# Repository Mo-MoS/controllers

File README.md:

# Controllers

## Description

Controllers for MIDI, USB, Software Synths, VST Plugins. 

## Pictures

**PCB boards for the 14 knobs of S2-OSC:**

**Functional prototype of S2-OSC in a livestream:**

**Paper scribble for the S2-OSC frontplate:**

**Prototype in handmade PCB boards for S2-OSC:**

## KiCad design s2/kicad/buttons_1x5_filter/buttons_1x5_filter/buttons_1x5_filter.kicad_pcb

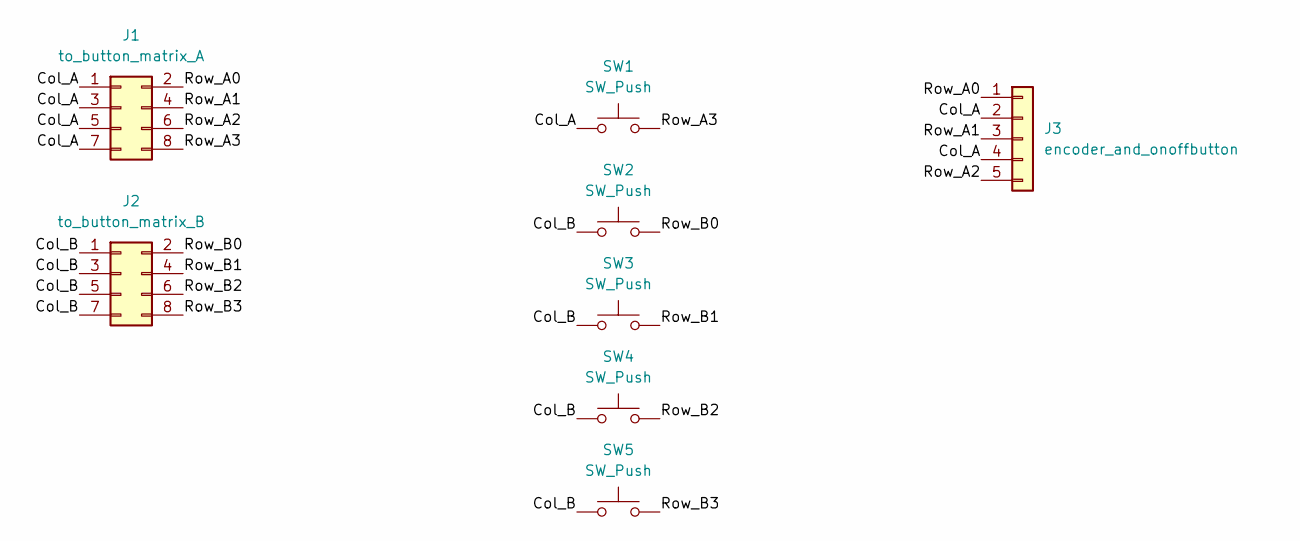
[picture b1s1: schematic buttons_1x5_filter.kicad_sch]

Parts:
J1: to_button_matrix_A; PinHeader_2x04_P2.54mm_Vertical
J2: to_button_matrix_B; PinHeader_2x04_P2.54mm_Vertical
J3: encoder_and_onoffbutton; PinHeader_1x05_P2.54mm_Vertical
SW1, SW2, SW3, SW4, SW5: SW_Push; SW_PUSH_6mm

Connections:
/Col_A: J1.1, J1.3, J1.5, J1.7, J3.2, J3.4, SW1.1
/Col_B: J2.1, J2.3, J2.5, J2.7, SW2.1, SW3.1, SW4.1, SW5.1
/Row_A0: J1.2, J3.1
/Row_A1: J1.4, J3.3
/Row_A2: J1.6, J3.5
/Row_A3: J1.8, SW1.2
/Row_B0: J2.2, SW2.2
/Row_B1: J2.4, SW3.2
/Row_B2: J2.6, SW4.2
/Row_B3: J2.8, SW5.2

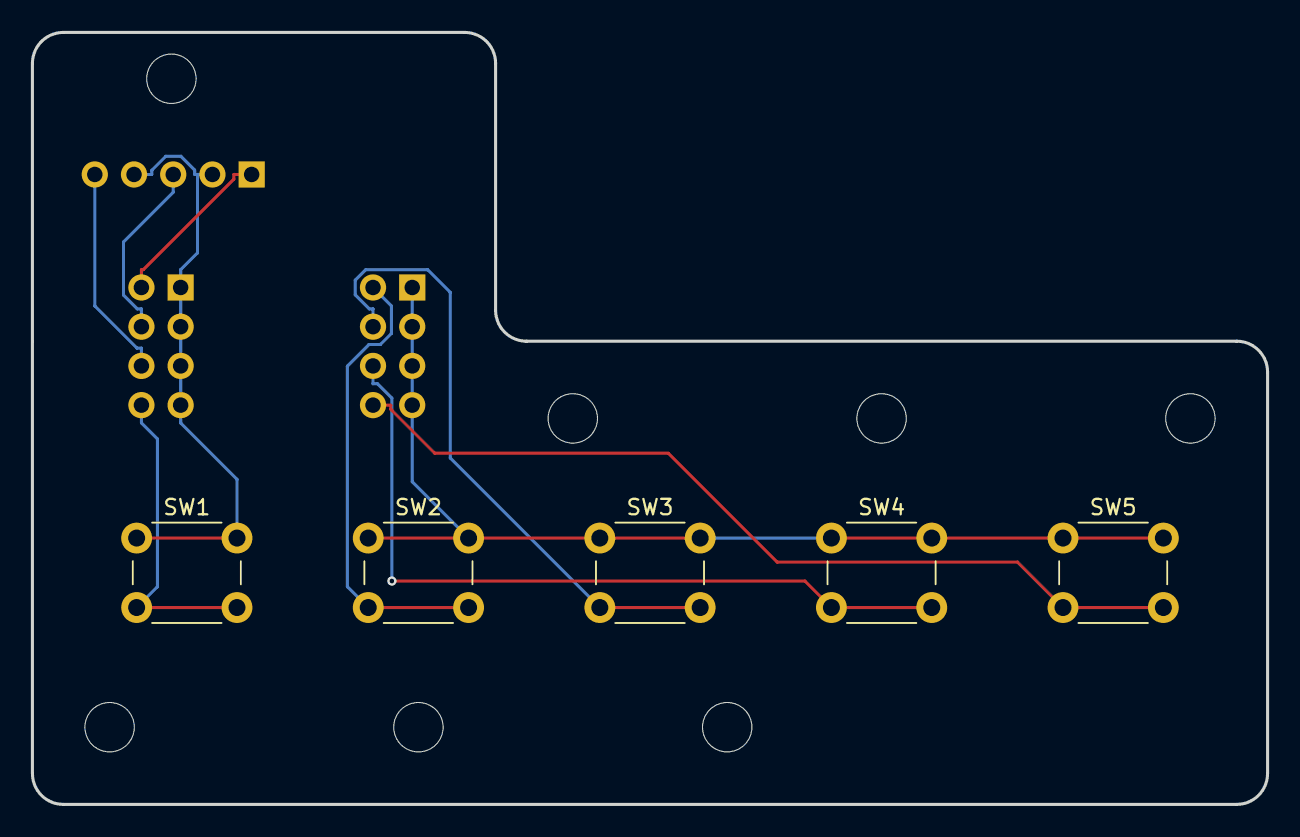
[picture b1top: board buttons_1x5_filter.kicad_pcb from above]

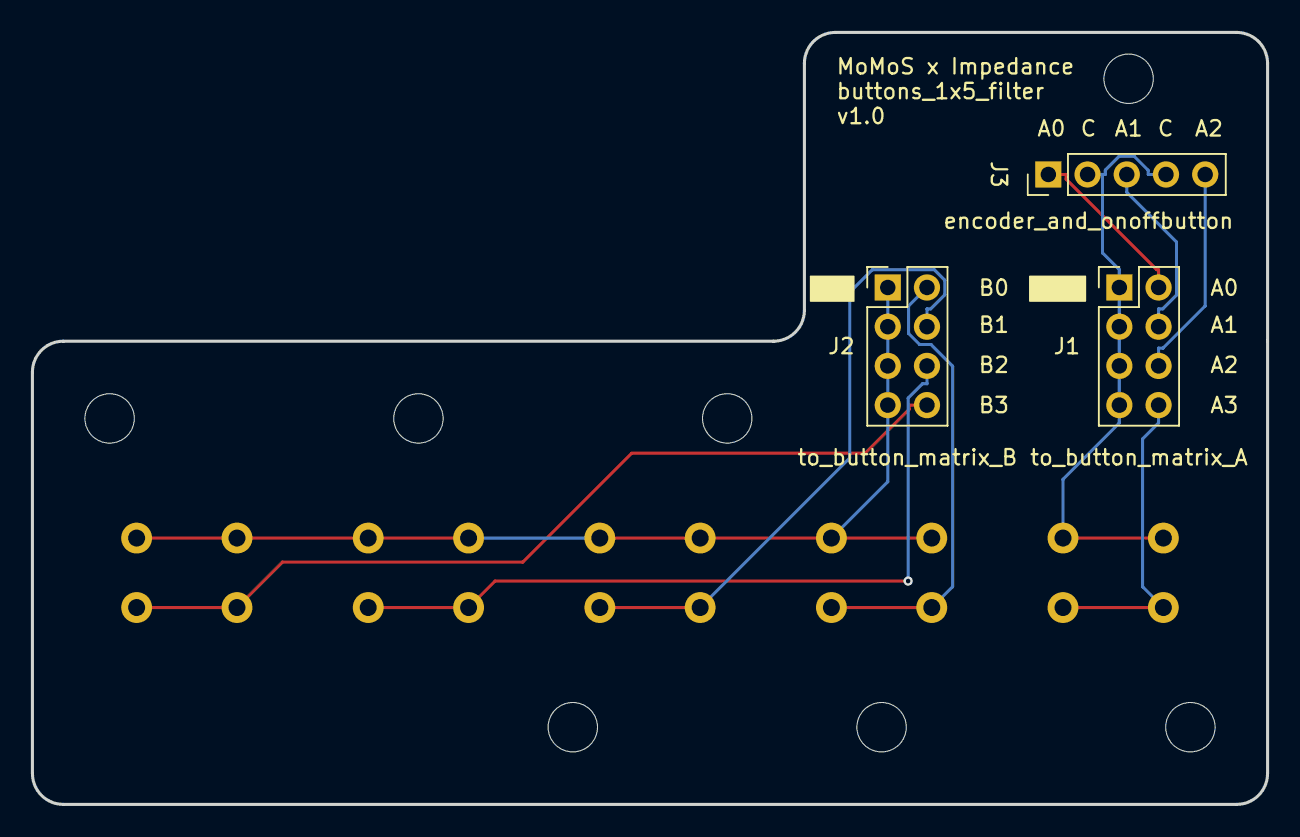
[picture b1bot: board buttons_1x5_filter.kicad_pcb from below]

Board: 2 copper layers, 80.0 x 50.0 mm, 8 parts (3 on the bottom side), 10 nets.

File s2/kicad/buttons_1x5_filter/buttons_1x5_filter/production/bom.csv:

Designator,Footprint,Quantity,Value,LCSC Part #
J1,PinHeader_2x04_P2.54mm_Vertical,1,to_button_matrix_A,
J2,PinHeader_2x04_P2.54mm_Vertical,1,to_button_matrix_B,
J3,PinHeader_1x05_P2.54mm_Vertical,1,encoder_and_onoffbutton,
"SW1, SW2, SW3, SW4, SW5",SW_PUSH_6mm,5,SW_Push,

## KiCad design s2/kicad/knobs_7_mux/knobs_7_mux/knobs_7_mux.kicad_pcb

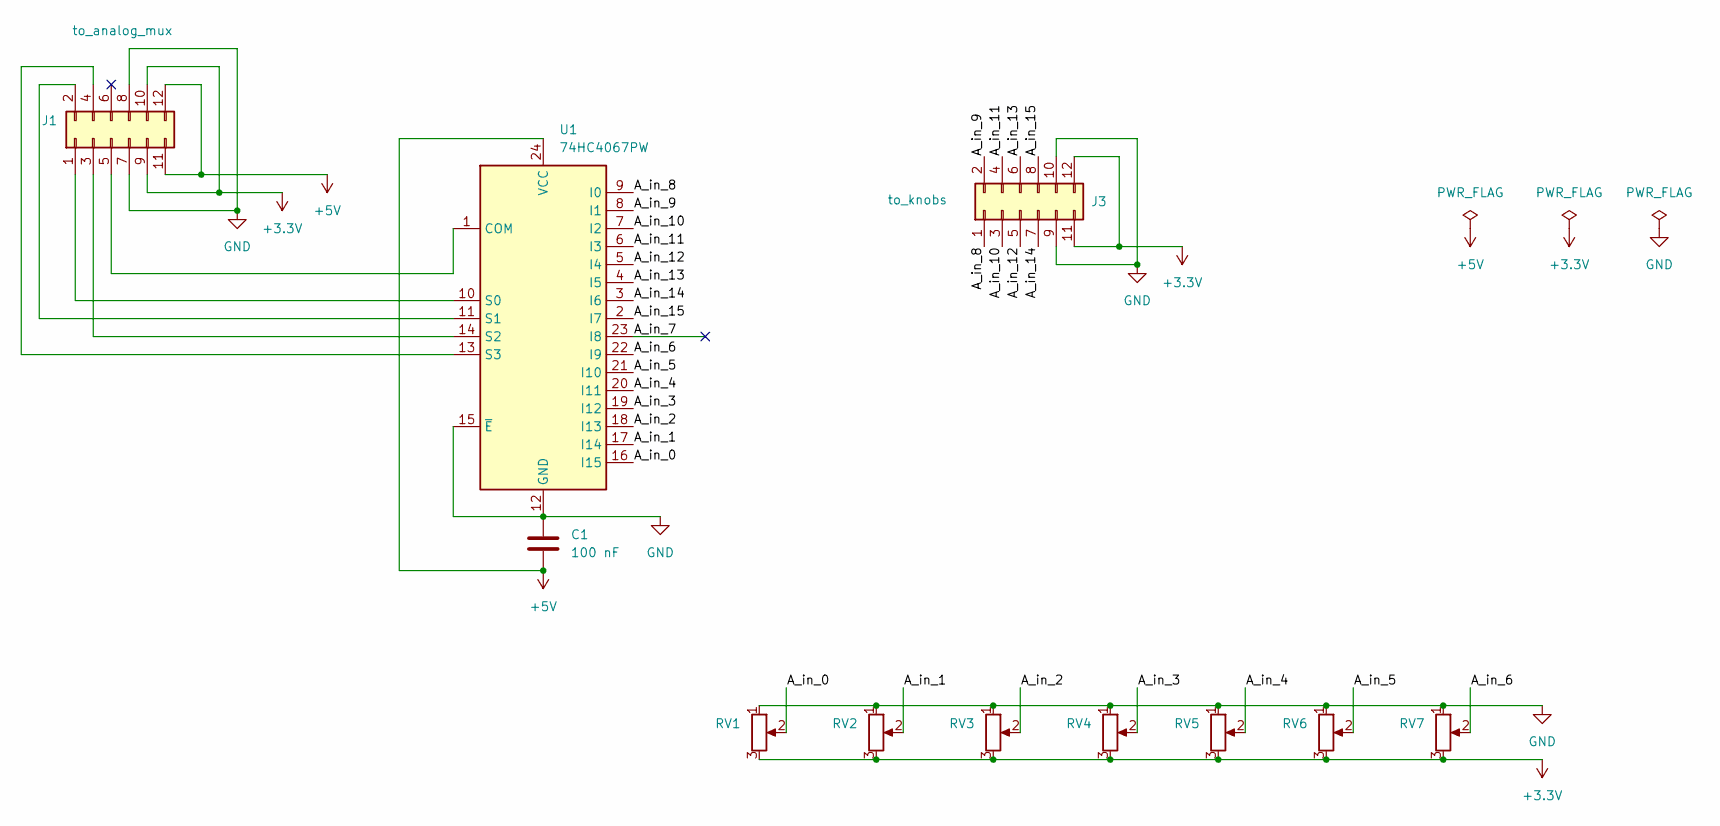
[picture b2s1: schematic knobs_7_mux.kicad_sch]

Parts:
C1: 100 nF; C_0402_1005Metric
J1: to_analog_mux; PinHeader_2x06_P2.54mm_Vertical
J3: to_knobs; PinHeader_2x06_P2.54mm_Vertical
RV1, RV2, RV3, RV4, RV5, RV6, RV7: R_Potentiometer; Potentiometer_RV09
U1: 74HC4067PW; SOP-24_7.5x15.4mm_P1.27mm

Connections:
+3.3V: J1.9, J1.10, J3.11, J3.12, RV1.3, RV2.3, RV3.3, RV4.3, RV5.3, RV6.3, RV7.3
+5V: C1.2, J1.11, J1.12, U1.24 (VCC)
/A_in_0: RV1.2, U1.16 (I15)
/A_in_1: RV2.2, U1.17 (I14)
/A_in_2: RV3.2, U1.18 (I13)
/A_in_3: RV4.2, U1.19 (I12)
/A_in_4: RV5.2, U1.20 (I11)
/A_in_5: RV6.2, U1.21 (I10)
/A_in_6: RV7.2, U1.22 (I9)
/A_in_7: U1.23 (I8)
/A_in_8: J3.1, U1.9 (I0)
/A_in_9: J3.2, U1.8 (I1)
/A_in_10: J3.3, U1.7 (I2)
/A_in_11: J3.4, U1.6 (I3)
/A_in_12: J3.5, U1.5 (I4)
/A_in_13: J3.6, U1.4 (I5)
/A_in_14: J3.7, U1.3 (I6)
/A_in_15: J3.8, U1.2 (I7)
GND: C1.1, J1.7, J1.8, J3.9, J3.10, RV1.1, RV2.1, RV3.1, RV4.1, RV5.1, RV6.1, RV7.1, U1.12 (GND), U1.15 (~E)
unnamed: J1.1, U1.10 (S0)
unnamed: J1.2, U1.11 (S1)
unnamed: J1.3, U1.14 (S2)
unnamed: J1.4, U1.13 (S3)
unnamed: J1.5, U1.1 (COM)

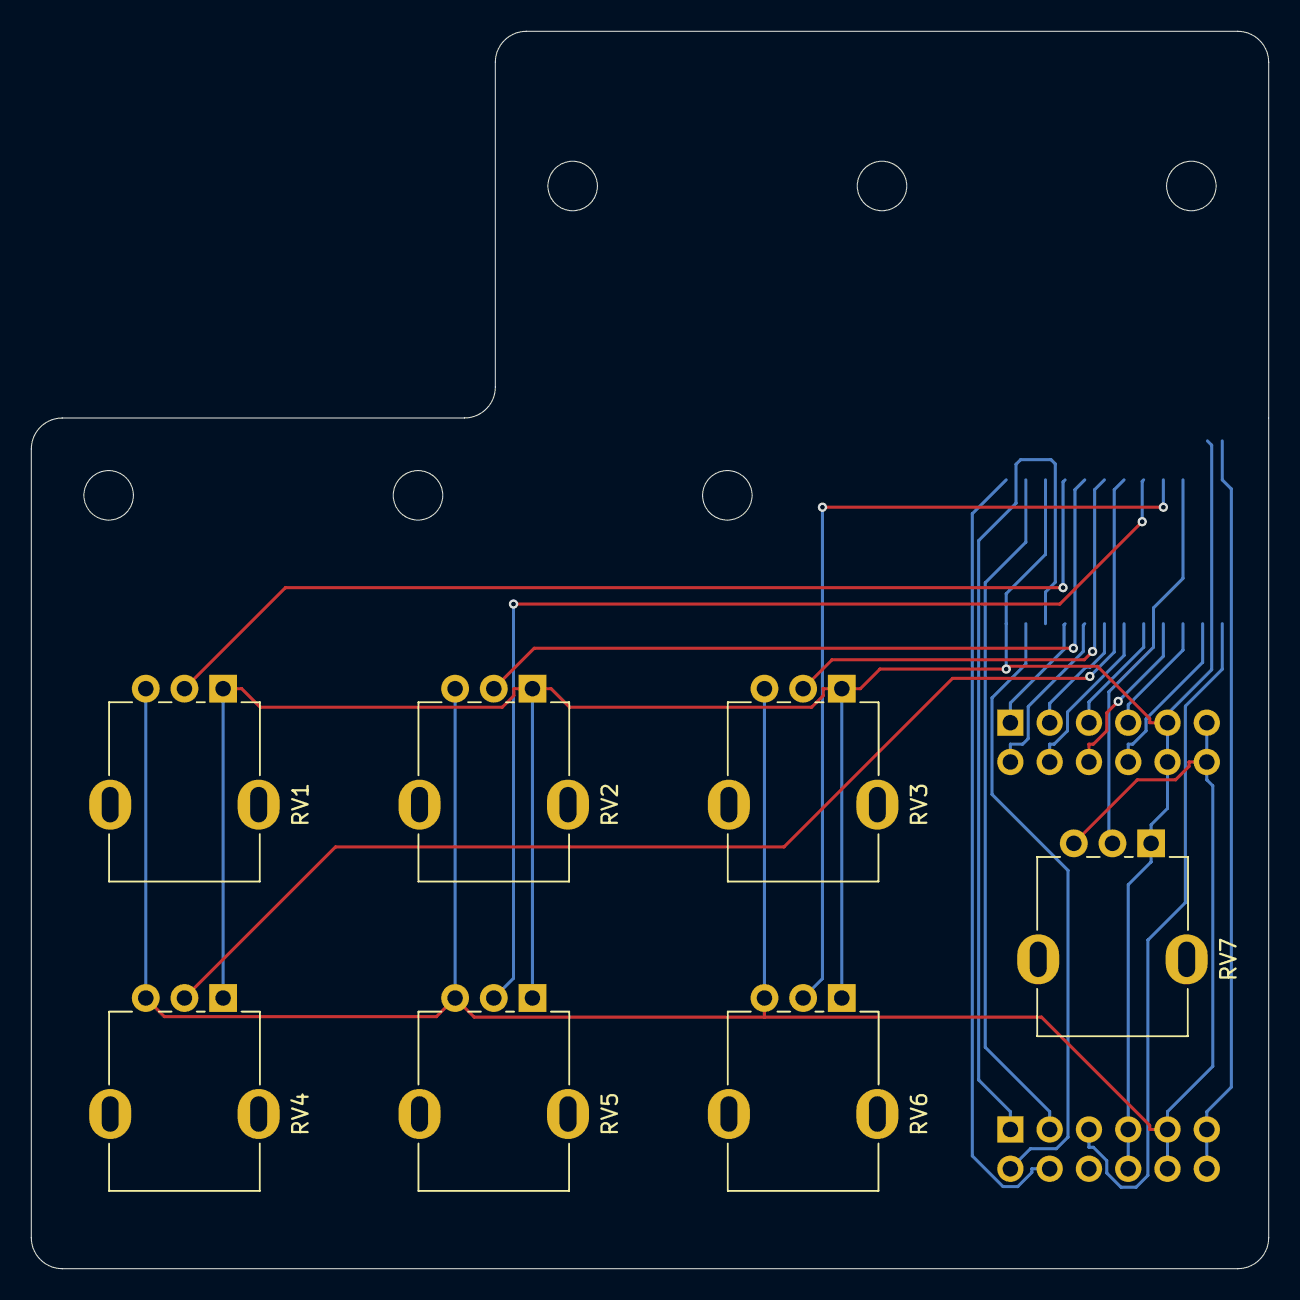
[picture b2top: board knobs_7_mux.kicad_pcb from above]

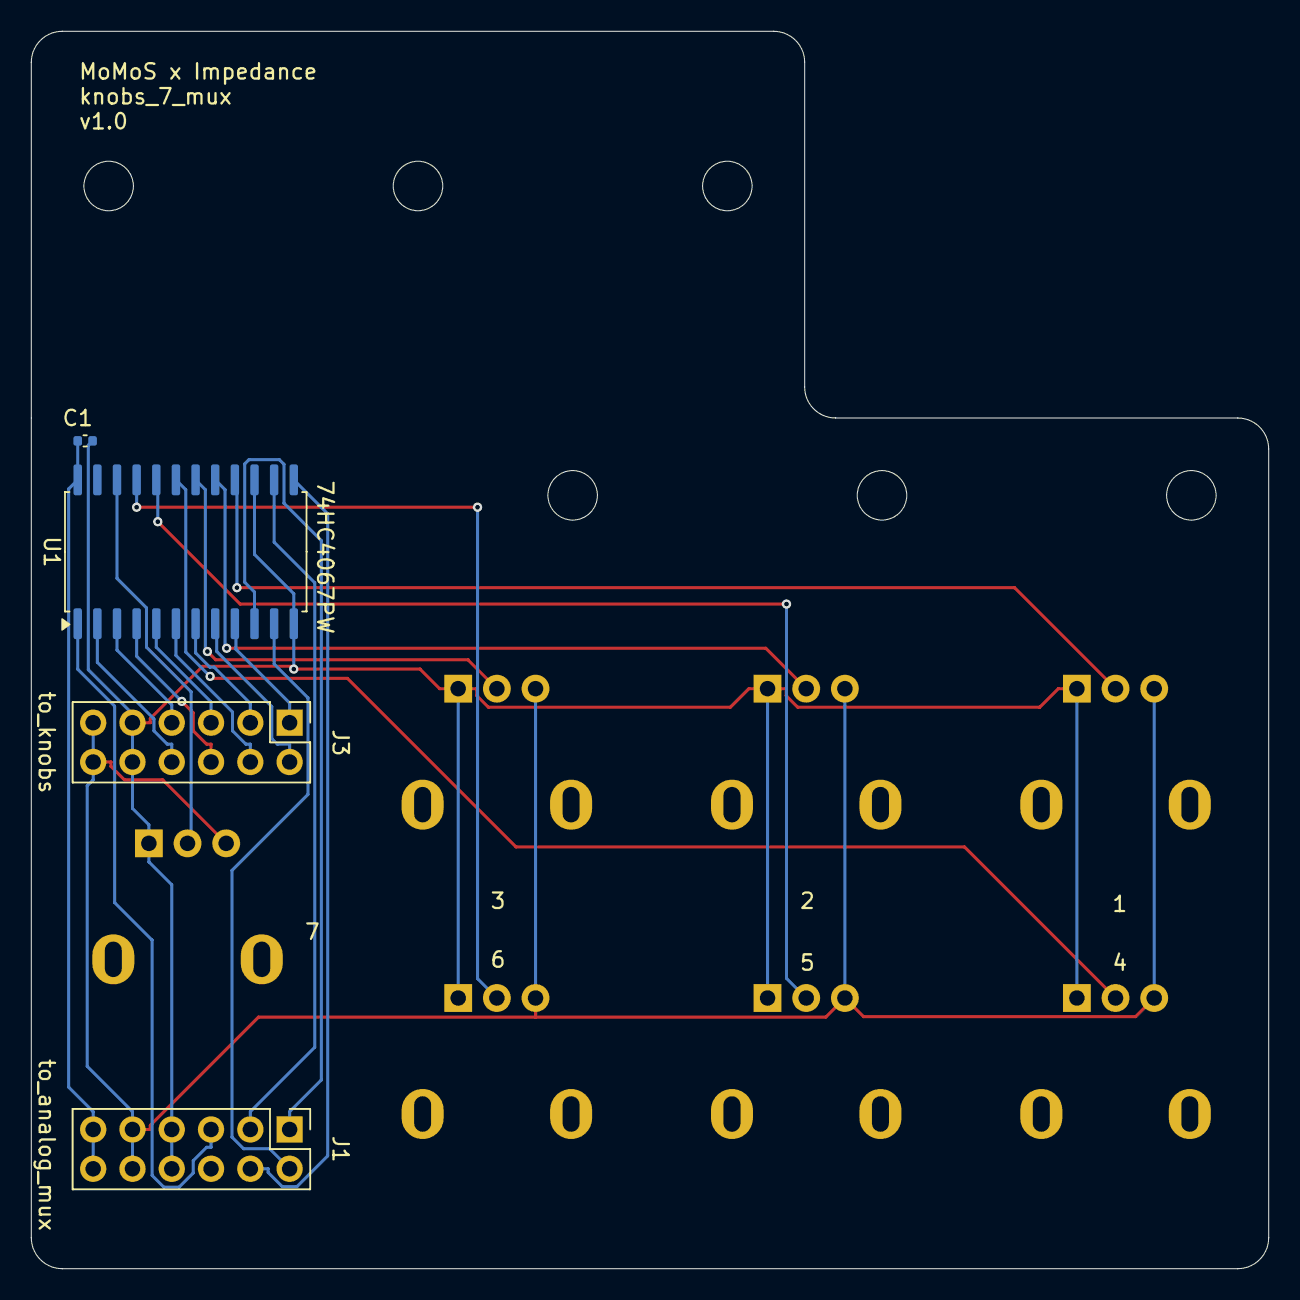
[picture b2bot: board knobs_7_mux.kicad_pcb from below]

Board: 2 copper layers, 80.0 x 80.0 mm, 11 parts (4 on the bottom side), 23 nets.

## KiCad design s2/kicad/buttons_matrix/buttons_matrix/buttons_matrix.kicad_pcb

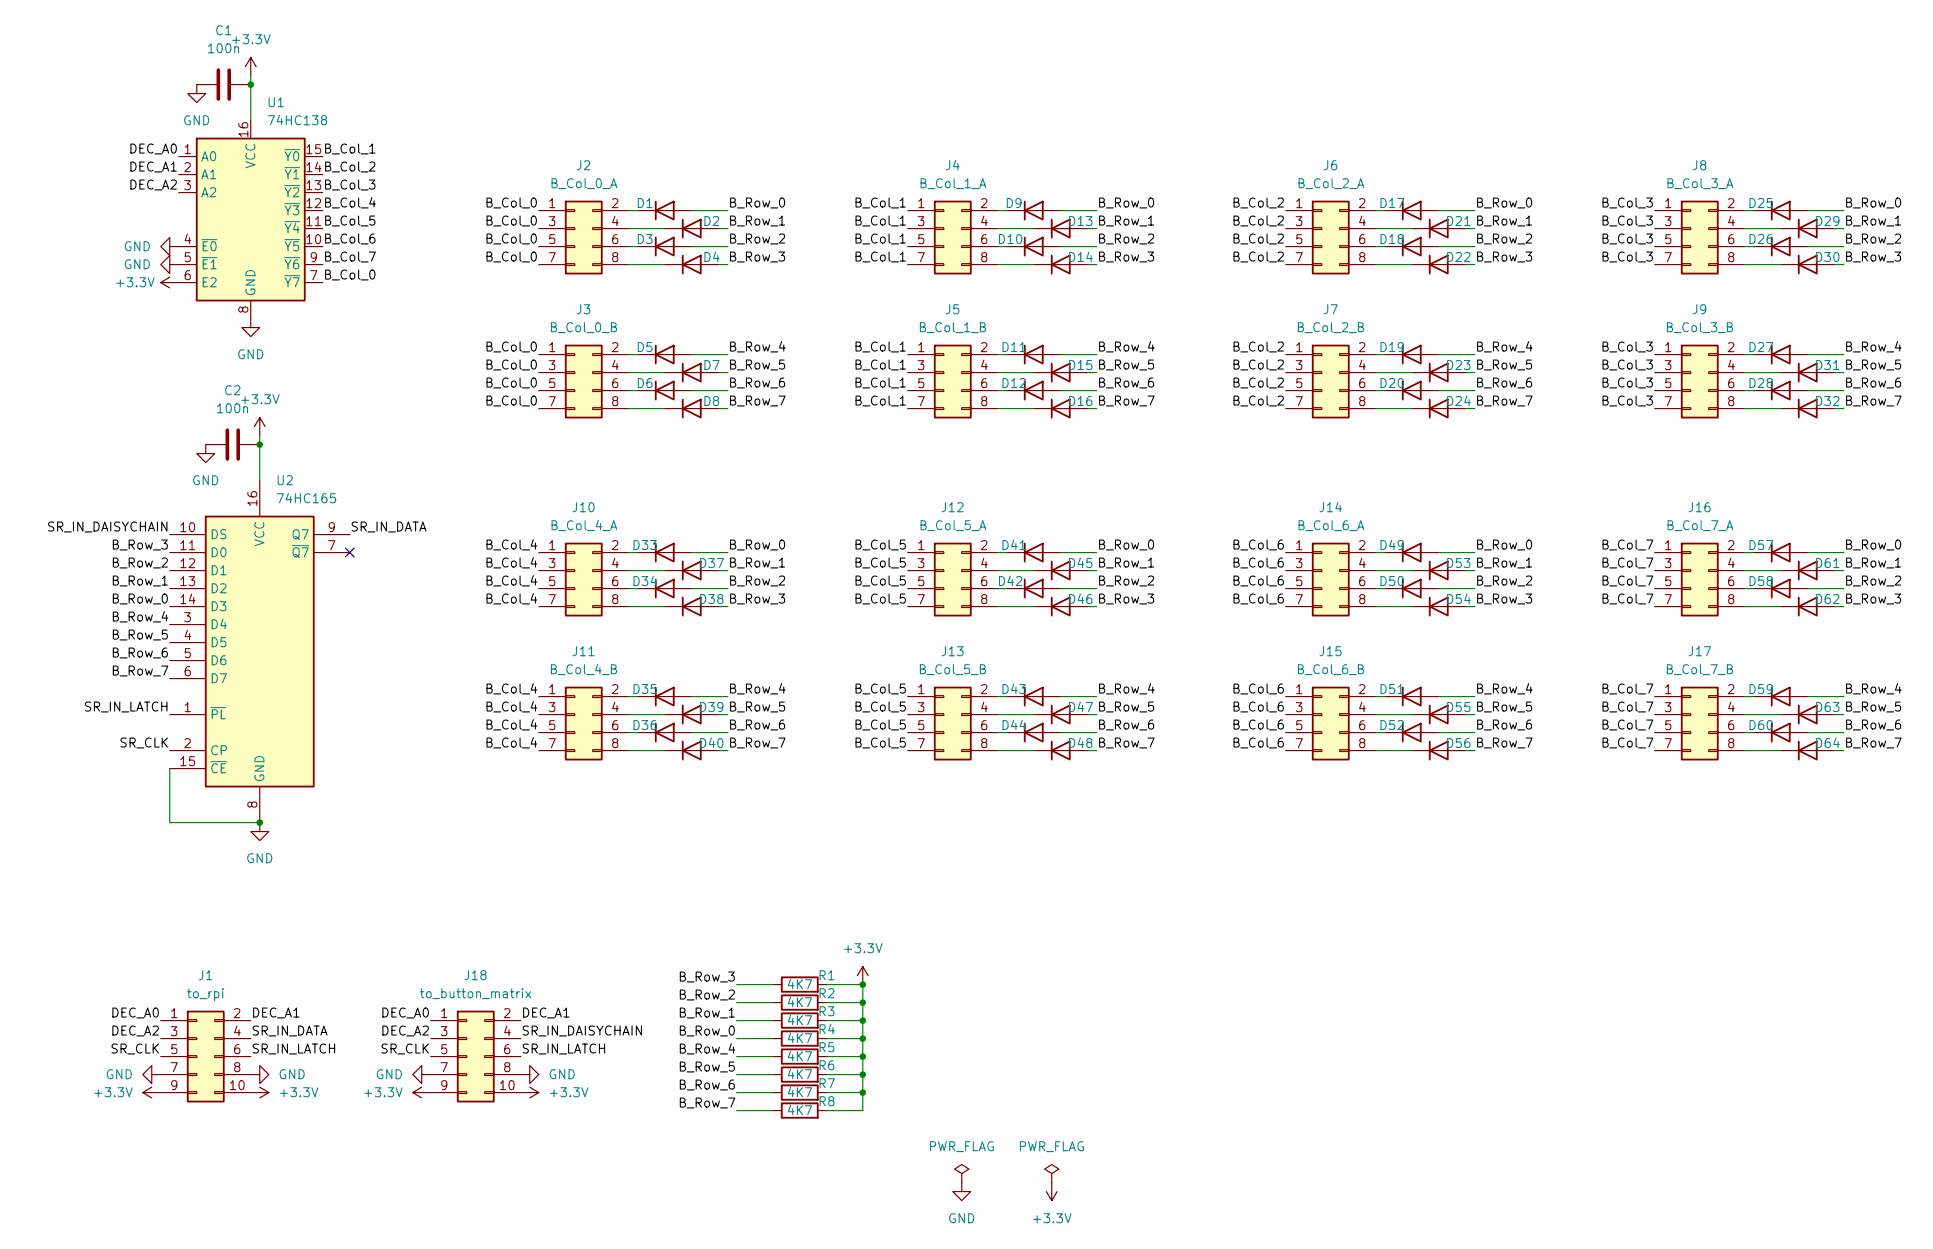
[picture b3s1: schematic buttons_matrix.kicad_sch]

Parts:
C1, C2: 100n; C_0603_1608Metric
D1, D2, D3, D4, D5, D6, D7, D8, D9, D10, D11, D12, D13, D14, D15, D16, D17, D18, D19, D20, D21, D22, D23, D24, D25, D26, D27, D28, D29, D30, D31, D32, D33, D34, D35, D36, D37, D38, D39, D40, D41, D42, D43, D44, D45, D46, D47, D48, D49, D50, D51, D52, D53, D54, D55, D56, D57, D58, D59, D60, D61, D62, D63, D64: 1N4148; D_SOD-323
J1: to_rpi; PinHeader_2x05_P2.54mm_Vertical
J2: B_Col_0_A; PinHeader_2x04_P2.54mm_Vertical
J3: B_Col_0_B; PinHeader_2x04_P2.54mm_Vertical
J4: B_Col_1_A; PinHeader_2x04_P2.54mm_Vertical
J5: B_Col_1_B; PinHeader_2x04_P2.54mm_Vertical
J6: B_Col_2_A; PinHeader_2x04_P2.54mm_Vertical
J7: B_Col_2_B; PinHeader_2x04_P2.54mm_Vertical
J8: B_Col_3_A; PinHeader_2x04_P2.54mm_Vertical
J9: B_Col_3_B; PinHeader_2x04_P2.54mm_Vertical
J10: B_Col_4_A; PinHeader_2x04_P2.54mm_Vertical
J11: B_Col_4_B; PinHeader_2x04_P2.54mm_Vertical
J12: B_Col_5_A; PinHeader_2x04_P2.54mm_Vertical
J13: B_Col_5_B; PinHeader_2x04_P2.54mm_Vertical
J14: B_Col_6_A; PinHeader_2x04_P2.54mm_Vertical
J15: B_Col_6_B; PinHeader_2x04_P2.54mm_Vertical
J16: B_Col_7_A; PinHeader_2x04_P2.54mm_Vertical
J17: B_Col_7_B; PinHeader_2x04_P2.54mm_Vertical
J18: to_button_matrix; PinHeader_2x05_P2.54mm_Vertical
R1, R2, R3, R4, R5, R6, R7, R8: 4K7; R_0603_1608Metric
U1: 74HC138; SOIC-16_3.9x9.9mm_P1.27mm
U2: 74HC165; SOIC-16_3.9x9.9mm_P1.27mm

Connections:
+3.3V: C1.2, C2.2, J1.9, J1.10, J18.9, J18.10, R1.2, R2.2, R3.2, R4.2, R5.2, R6.2, R7.2, R8.2, U1.6 (E2), U1.16 (VCC), U2.16 (VCC)
/B_Col_0: J2.1, J2.3, J2.5, J2.7, J3.1, J3.3, J3.5, J3.7, U1.7 (~Y7)
/B_Col_1: J4.1, J4.3, J4.5, J4.7, J5.1, J5.3, J5.5, J5.7, U1.15 (~Y0)
/B_Col_2: J6.1, J6.3, J6.5, J6.7, J7.1, J7.3, J7.5, J7.7, U1.14 (~Y1)
/B_Col_3: J8.1, J8.3, J8.5, J8.7, J9.1, J9.3, J9.5, J9.7, U1.13 (~Y2)
/B_Col_4: J10.1, J10.3, J10.5, J10.7, J11.1, J11.3, J11.5, J11.7, U1.12 (~Y3)
/B_Col_5: J12.1, J12.3, J12.5, J12.7, J13.1, J13.3, J13.5, J13.7, U1.11 (~Y4)
/B_Col_6: J14.1, J14.3, J14.5, J14.7, J15.1, J15.3, J15.5, J15.7, U1.10 (~Y5)
/B_Col_7: J16.1, J16.3, J16.5, J16.7, J17.1, J17.3, J17.5, J17.7, U1.9 (~Y6)
/B_Row_0: D1.2 (A), D9.2 (A), D17.2 (A), D25.2 (A), D33.2 (A), D41.2 (A), D49.2 (A), D57.2 (A), R4.1, U2.14 (D3)
/B_Row_1: D2.2 (A), D13.2 (A), D21.2 (A), D29.2 (A), D37.2 (A), D45.2 (A), D53.2 (A), D61.2 (A), R3.1, U2.13 (D2)
/B_Row_2: D3.2 (A), D10.2 (A), D18.2 (A), D26.2 (A), D34.2 (A), D42.2 (A), D50.2 (A), D58.2 (A), R2.1, U2.12 (D1)
/B_Row_3: D4.2 (A), D14.2 (A), D22.2 (A), D30.2 (A), D38.2 (A), D46.2 (A), D54.2 (A), D62.2 (A), R1.1, U2.11 (D0)
/B_Row_4: D5.2 (A), D11.2 (A), D19.2 (A), D27.2 (A), D35.2 (A), D43.2 (A), D51.2 (A), D59.2 (A), R5.1, U2.3 (D4)
/B_Row_5: D7.2 (A), D15.2 (A), D23.2 (A), D31.2 (A), D39.2 (A), D47.2 (A), D55.2 (A), D63.2 (A), R6.1, U2.4 (D5)
/B_Row_6: D6.2 (A), D12.2 (A), D20.2 (A), D28.2 (A), D36.2 (A), D44.2 (A), D52.2 (A), D60.2 (A), R7.1, U2.5 (D6)
/B_Row_7: D8.2 (A), D16.2 (A), D24.2 (A), D32.2 (A), D40.2 (A), D48.2 (A), D56.2 (A), D64.2 (A), R8.1, U2.6 (D7)
/DEC_A0: J1.1, J18.1, U1.1 (A0)
/DEC_A1: J1.2, J18.2, U1.2 (A1)
/DEC_A2: J1.3, J18.3, U1.3 (A2)
/SR_CLK: J1.5, J18.5, U2.2 (CP)
/SR_IN_DAISYCHAIN: J18.4, U2.10 (DS)
/SR_IN_DATA: J1.4, U2.9 (Q7)
/SR_IN_LATCH: J1.6, J18.6, U2.1 (~PL)
GND: C1.1, C2.1, J1.7, J1.8, J18.7, J18.8, U1.4 (~E0), U1.5 (~E1), U1.8 (GND), U2.8 (GND), U2.15 (~CE)
unnamed: D1.1 (K), J2.2
unnamed: D2.1 (K), J2.4
unnamed: D3.1 (K), J2.6
unnamed: D4.1 (K), J2.8
unnamed: D5.1 (K), J3.2
unnamed: D6.1 (K), J3.6
unnamed: D7.1 (K), J3.4
unnamed: D8.1 (K), J3.8
unnamed: D9.1 (K), J4.2
unnamed: D10.1 (K), J4.6
unnamed: D11.1 (K), J5.2
unnamed: D12.1 (K), J5.6
unnamed: D13.1 (K), J4.4
unnamed: D14.1 (K), J4.8
unnamed: D15.1 (K), J5.4
unnamed: D16.1 (K), J5.8
unnamed: D17.1 (K), J6.2
unnamed: D18.1 (K), J6.6
unnamed: D19.1 (K), J7.2
unnamed: D20.1 (K), J7.6
unnamed: D21.1 (K), J6.4
unnamed: D22.1 (K), J6.8
unnamed: D23.1 (K), J7.4
unnamed: D24.1 (K), J7.8
unnamed: D25.1 (K), J8.2
unnamed: D26.1 (K), J8.6
unnamed: D27.1 (K), J9.2
unnamed: D28.1 (K), J9.6
unnamed: D29.1 (K), J8.4
unnamed: D30.1 (K), J8.8
unnamed: D31.1 (K), J9.4
unnamed: D32.1 (K), J9.8
unnamed: D33.1 (K), J10.2
unnamed: D34.1 (K), J10.6
unnamed: D35.1 (K), J11.2
unnamed: D36.1 (K), J11.6
unnamed: D37.1 (K), J10.4
unnamed: D38.1 (K), J10.8
unnamed: D39.1 (K), J11.4
unnamed: D40.1 (K), J11.8
unnamed: D41.1 (K), J12.2
unnamed: D42.1 (K), J12.6
unnamed: D43.1 (K), J13.2
unnamed: D44.1 (K), J13.6
unnamed: D45.1 (K), J12.4
unnamed: D46.1 (K), J12.8
unnamed: D47.1 (K), J13.4
unnamed: D48.1 (K), J13.8
unnamed: D49.1 (K), J14.2
unnamed: D50.1 (K), J14.6
unnamed: D51.1 (K), J15.2
unnamed: D52.1 (K), J15.6
unnamed: D53.1 (K), J14.4
unnamed: D54.1 (K), J14.8
unnamed: D55.1 (K), J15.4
unnamed: D56.1 (K), J15.8
unnamed: D57.1 (K), J16.2
unnamed: D58.1 (K), J16.6
unnamed: D59.1 (K), J17.2
unnamed: D60.1 (K), J17.6
unnamed: D61.1 (K), J16.4
unnamed: D62.1 (K), J16.8
unnamed: D63.1 (K), J17.4
unnamed: D64.1 (K), J17.8

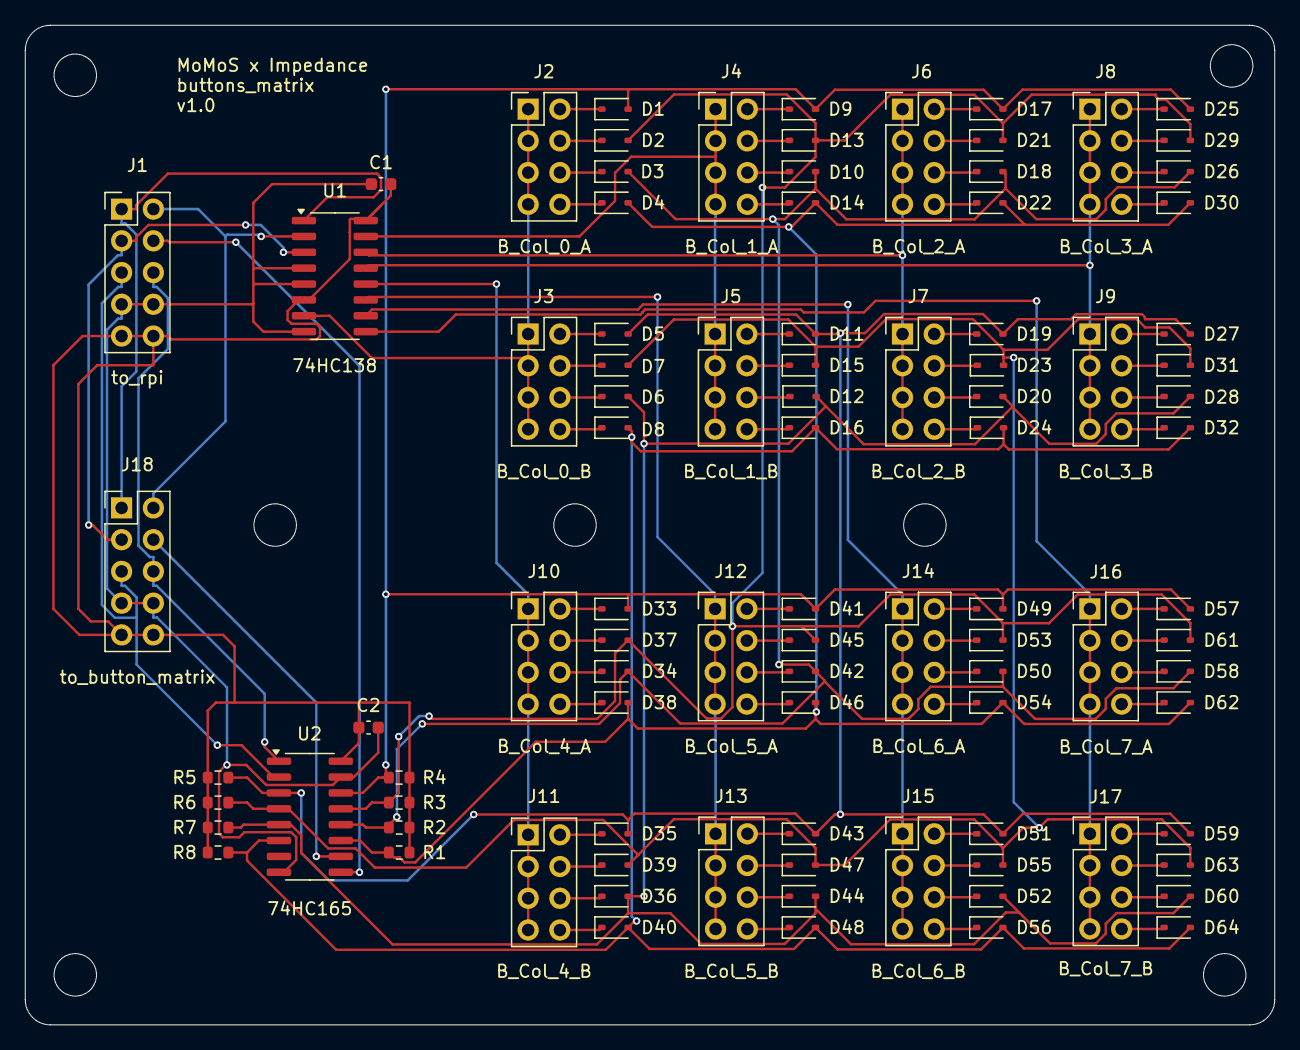
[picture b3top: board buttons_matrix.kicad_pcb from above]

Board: 2 copper layers, 100.0 x 80.0 mm, 94 parts (0 on the bottom side), 89 nets.

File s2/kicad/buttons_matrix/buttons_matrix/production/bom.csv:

Designator,Footprint,Quantity,Value,LCSC Part #
"C1, C2",603,2,100n,
"D1, D10, D11, D12, D13, D14, D15, D16, D17, D18, D19, D2, D20, D21, D22, D23, D24, D25, D26, D27, D28, D29, D3, D30, D31, D32, D33, D34, D35, D36, D37, D38, D39, D4, D40, D41, D42, D43, D44, D45, D46, D47, D48, D49, D5, D50, D51, D52, D53, D54, D55, D56, D57, D58, D59, D6, D60, D61, D62, D63, D64, D7, D8, D9",D_SOD-323,64,1N4148,
"R1, R2, R3, R4, R5, R6, R7, R8",603,8,4K7,
U1,SOIC-16_3.9x9.9mm_P1.27mm,1,74HC138,
U2,SOIC-16_3.9x9.9mm_P1.27mm,1,74HC165,

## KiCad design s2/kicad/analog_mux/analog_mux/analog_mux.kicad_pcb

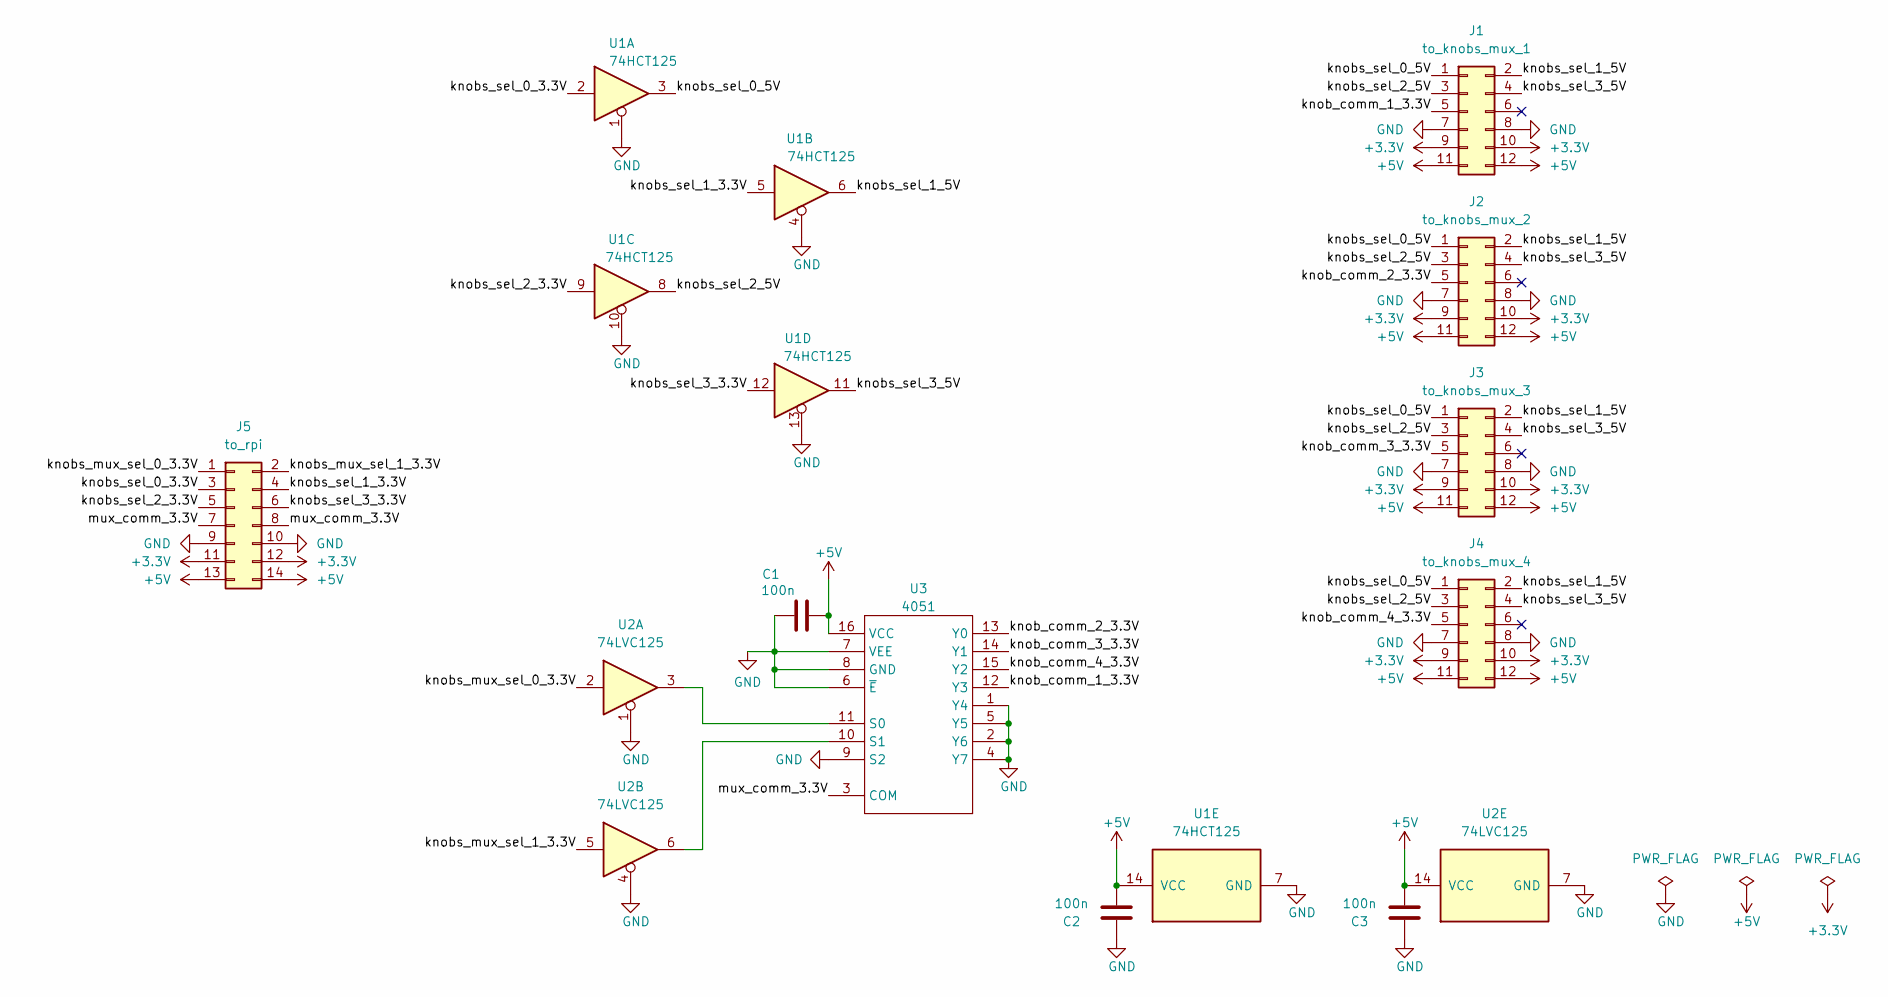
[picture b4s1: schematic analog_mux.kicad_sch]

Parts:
C1, C2, C3: 100n; C_0402_1005Metric; LCSC C1525
J1: to_knobs_mux_1; PinHeader_2x06_P2.54mm_Horizontal
J2: to_knobs_mux_2; PinHeader_2x06_P2.54mm_Horizontal
J3: to_knobs_mux_3; PinHeader_2x06_P2.54mm_Horizontal
J4: to_knobs_mux_4; PinHeader_2x06_P2.54mm_Horizontal
J5: to_rpi; PinHeader_2x07_P2.54mm_Horizontal
U1: 74HCT125; SO-14_5.3x10.2mm_P1.27mm
U2: 74LVC125; SO-14_5.3x10.2mm_P1.27mm
U3: 4051; DIP-16_W7.62mm_Socket_LongPads; LCSC C9386

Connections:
+3.3V: J1.9, J1.10, J2.9, J2.10, J3.9, J3.10, J4.9, J4.10, J5.11, J5.12
+5V: C1.2, C2.2, C3.2, J1.11, J1.12, J2.11, J2.12, J3.11, J3.12, J4.11, J4.12, J5.13, J5.14, U1.14 (VCC), U2.14 (VCC), U3.16 (VCC)
/knob_comm_1_3.3V: J1.5, U3.12 (Y3)
/knob_comm_2_3.3V: J2.5, U3.13 (Y0)
/knob_comm_3_3.3V: J3.5, U3.14 (Y1)
/knob_comm_4_3.3V: J4.5, U3.15 (Y2)
/knobs_mux_sel_0_3.3V: J5.1, U2.2
/knobs_mux_sel_1_3.3V: J5.2, U2.5
/knobs_sel_0_3.3V: J5.3, U1.2
/knobs_sel_0_5V: J1.1, J2.1, J3.1, J4.1, U1.3
/knobs_sel_1_3.3V: J5.4, U1.5
/knobs_sel_1_5V: J1.2, J2.2, J3.2, J4.2, U1.6
/knobs_sel_2_3.3V: J5.5, U1.9
/knobs_sel_2_5V: J1.3, J2.3, J3.3, J4.3, U1.8
/knobs_sel_3_3.3V: J5.6, U1.12
/knobs_sel_3_5V: J1.4, J2.4, J3.4, J4.4, U1.11
/mux_comm_3.3V: J5.7, J5.8, U3.3 (COM)
GND: C1.1, C2.1, C3.1, J1.7, J1.8, J2.7, J2.8, J3.7, J3.8, J4.7, J4.8, J5.9, J5.10, U1.1, U1.4, U1.7 (GND), U1.10, U1.13, U2.1, U2.4, U2.7 (GND), U3.1 (Y4), U3.2 (Y6), U3.4 (Y7), U3.5 (Y5), U3.6 (~E), U3.7 (VEE), U3.8 (GND), U3.9 (S2)
unnamed: U2.3, U3.11 (S0)
unnamed: U2.6, U3.10 (S1)

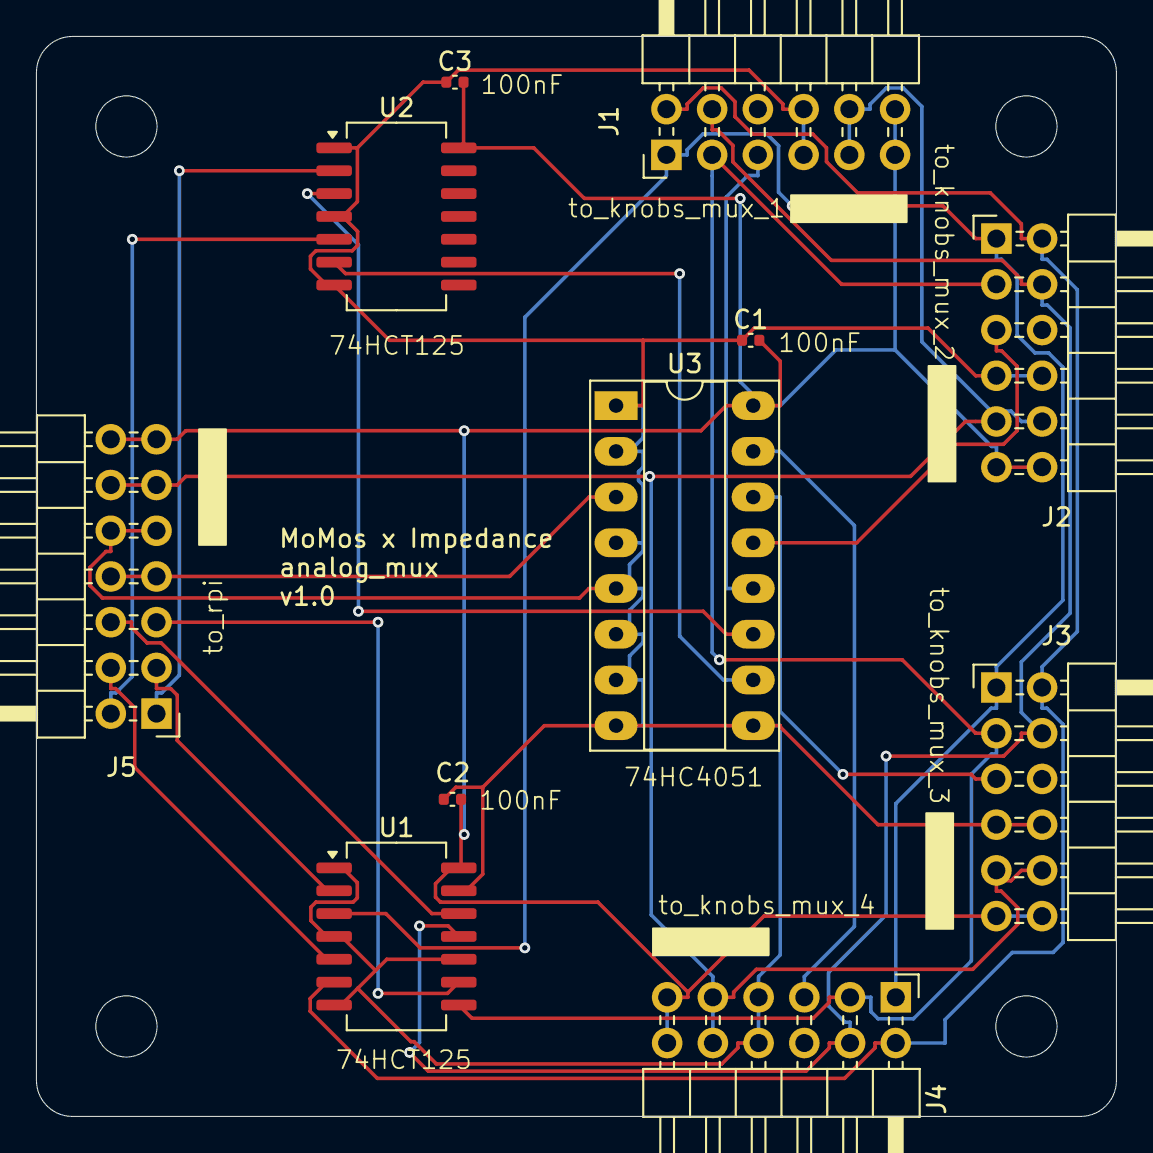
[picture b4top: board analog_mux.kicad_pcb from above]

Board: 2 copper layers, 60.0 x 60.0 mm, 11 parts (0 on the bottom side), 20 nets.

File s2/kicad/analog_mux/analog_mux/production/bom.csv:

Designator,Footprint,Quantity,Value,LCSC Part #
"C1, C2, C3",0402,3,100n,C1525
J1,PinHeader_2x06_P2.54mm_Horizontal,1,to_knobs_mux_1,
J2,PinHeader_2x06_P2.54mm_Horizontal,1,to_knobs_mux_2,
J3,PinHeader_2x06_P2.54mm_Horizontal,1,to_knobs_mux_3,
J4,PinHeader_2x06_P2.54mm_Horizontal,1,to_knobs_mux_4,
J5,PinHeader_2x07_P2.54mm_Horizontal,1,to_rpi,
U1,SO-14_5.3x10.2mm_P1.27mm,1,74HCT125,
U2,SO-14_5.3x10.2mm_P1.27mm,1,74LVC125,
U3,DIP-16_W7.62mm_Socket_LongPads,1,4051,C9386

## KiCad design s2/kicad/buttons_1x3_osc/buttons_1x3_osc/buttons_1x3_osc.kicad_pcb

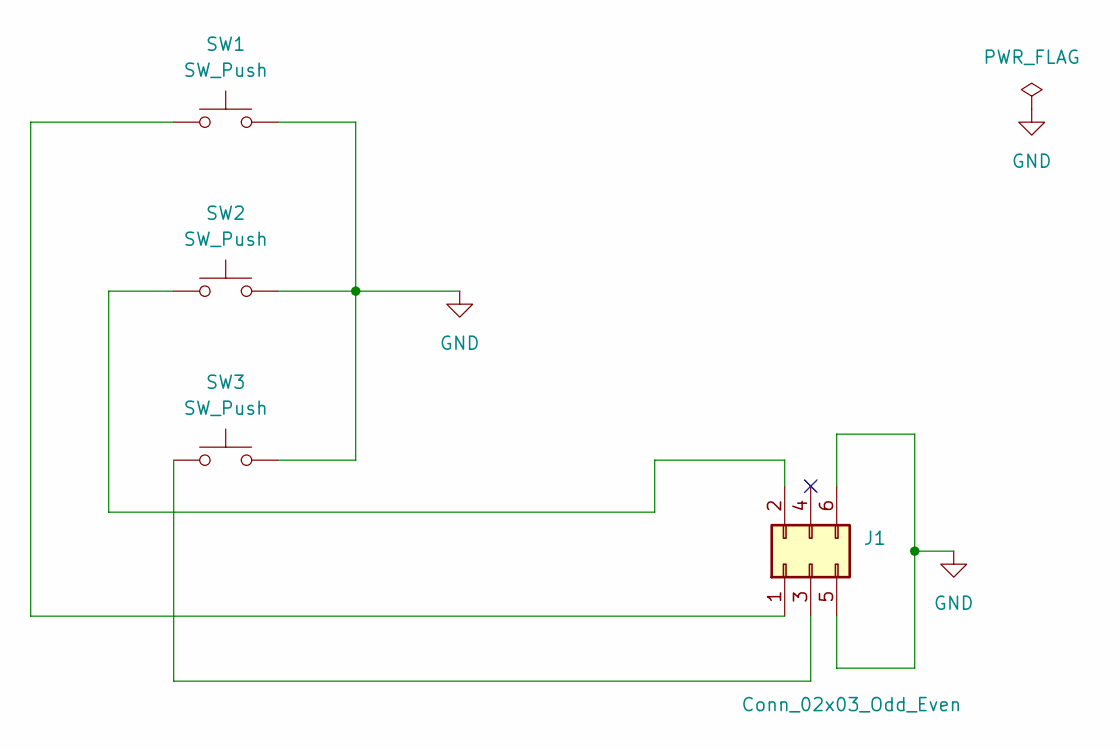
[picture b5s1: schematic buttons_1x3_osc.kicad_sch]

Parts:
J1: Conn_02x03_Odd_Even; PinHeader_2x03_P2.54mm_Horizontal
SW1, SW2, SW3: SW_Push; SW_PUSH_6mm

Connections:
GND: J1.5, J1.6, SW1.2, SW2.2, SW3.2
unnamed: J1.1, SW1.1
unnamed: J1.2, SW2.1
unnamed: J1.3, SW3.1

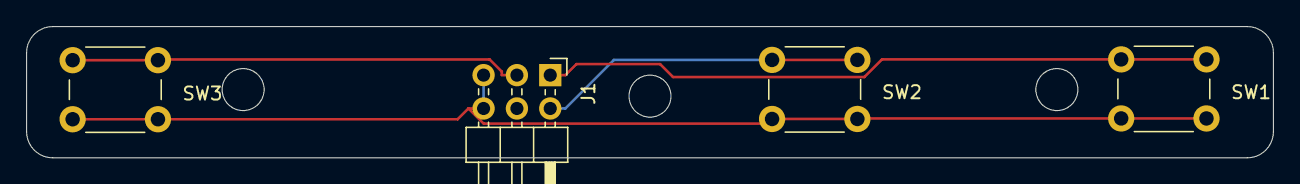
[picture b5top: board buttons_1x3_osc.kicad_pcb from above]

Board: 2 copper layers, 95.0 x 10.0 mm, 4 parts (0 on the bottom side), 4 nets.

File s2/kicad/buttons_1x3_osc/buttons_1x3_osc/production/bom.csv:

Designator,Footprint,Quantity,Value,LCSC Part #
J1,PinHeader_2x03_P2.54mm_Horizontal,1,Conn_02x03_Odd_Even,
"SW1, SW2, SW3",SW_PUSH_6mm,3,SW_Push,
